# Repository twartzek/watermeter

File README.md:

# WatermeterAI NextGen 💧

Turns a photo of an ordinary analog water meter into a continuous digital reading — no smart meter, no retrofit, just a Raspberry Pi, a camera, and a YOLO model reading the dials like a person would.

Every 15 minutes, a camera photographs the meter's dial face and a pair of YOLO models reads the digit wheels and sweep needles into one cumulative value, which is filtered for outliers, stored, and pushed to a dashboard and MQTT. A nightly job watches the trend for the signature of a leak and emails a warning before it becomes a water bill.

## Contents

- [WatermeterAI NextGen 💧](#watermeterai-nextgen-)
  - [Contents](#contents)
  - [Installation](#installation)
  - [Local development](#local-development)
    - [Verifying a deploy](#verifying-a-deploy)
  - [Configuration reference](#configuration-reference)
  - [How it works](#how-it-works)
  - [Model training](#model-training)
  - [Hardware](#hardware)
    - [What it costs](#what-it-costs)
  - [Leak detection](#leak-detection)
  - [Repository layout](#repository-layout)
  - [Known limitations](#known-limitations)
  - [Credits](#credits)
  - [License](#license)

## Installation

The intended target is a fresh Raspberry Pi OS install (Bullseye or newer, 64-bit recommended for `torch`/`ultralytics`).

```bash
git clone https://github.com/twartzek/watermeter
cd watermeter
sudo bash setupscript.sh
```

`setupscript.sh` is idempotent-ish but not fully — read it before running it twice. It will:

1. Increase swap to 2 GB (YOLO inference is memory-hungry on a Pi Zero 2)
2. Install system packages (`python3-picamera2`, `zbar-tools`, `npm`, `watchdog`)
3. Create a Python venv and install the pinned backend dependencies
4. Write `/home/admin/watermeter/.env` with the paths the backend expects
5. Register two `systemd` services and three cron jobs (measurement every 15 min, leak check nightly, photo cleanup nightly)
   - Readings are kept at full 15-minute resolution forever. At ~100 bytes per row that is only ~4 MB per year, and the leak detector's baseline window (`BASELINE_LOOKBACK_DAYS`, currently 30 days) can be extended if needed.
   - The photos are what fills the SD card, so the nightly cleanup keeps every photo for the last 30 days only. On older days it keeps just the photos of the first and last reading, and it also removes older orphaned photos from failed recognitions.
6. Configure a hardware watchdog that reboots the Pi if the reading log goes stale

Build the frontend once, so the systemd service has something to serve:

```bash
cd frontend
npm install
npm run build   # outputs to frontend/dist, served by `serve` on :80
```

On first boot with no WiFi configured, `backend/wifi.py` waits for a WiFi-credentials QR code (printed on a router, or from any "share WiFi" phone feature) to be shown to the camera — no keyboard or monitor needed.

## Local development

No Pi or camera needed to work on the dashboard/API — `requirements.txt` covers everything else:

```bash
cd backend
python3 -m venv .venv && source .venv/bin/activate
pip install -r requirements.txt

cp .env.example watermeter/.env   # see Configuration reference below
python seed_dev_data.py           # optional: populate SQLite with sample readings
python restapi.py                 # → http://localhost:8000/api/v1
```

```bash
cd frontend
npm install
npm run dev                       # → http://localhost:5173
```

Run the test suite with:

```bash
cd backend
pytest
```

`requirements-pi.txt` (`ultralytics`, `torch`, `opencv-python`, `pyzbar`, `Pillow`) is only needed for the actual image-reading pipeline, on hardware that can run YOLO inference.

### Verifying a deploy

Every frontend build stamps itself with its short git commit hash (`git rev-parse --short HEAD` in [`frontend/vite.config.js`](frontend/vite.config.js), plus `-dirty` for uncommitted changes), shown at the bottom of the dashboard sidebar — compare it against your local `git rev-parse --short HEAD` after `deploy.sh` to confirm the Pi picked up the latest build.

## Configuration reference

Install-specific config lives in two places, both deliberately excluded from version control:

| File | Holds | Set by |
|---|---|---|
| `watermeter/.env` | Filesystem paths — DB file, image folder, log folder, model weight paths | `setupscript.sh` on install |
| `data/settings.json` | MQTT broker credentials, SMTP credentials | Dashboard's Settings page, or manually on first run |

> **Network exposure:** The REST API has permissive CORS and no authentication — built for a trusted home LAN. Don't port-forward `:8000`/`:80` without a reverse proxy and auth in front.

## How it works

```mermaid
flowchart TB
    cam["📷 Pi Camera<br/><small>every 15 min</small>"]
    read["readTotalConsumption.py<br/><small>2× YOLO11<br/>digits + needles</small>"]
    presence["missing-box check<br/><small>discard incomplete reads</small>"]
    filt["outlierDetection.py<br/><small>digit · flow · delta<br/>filters</small>"]
    db[("SQLite<br/><small>readings + images</small>")]
    mqtt["MQTT broker"]
    api["restapi.py<br/><small>FastAPI :8000</small>"]
    dash["React dashboard<br/><small>:80</small>"]
    leak["leakageDetector.py<br/><small>Z-score + Isolation<br/>Forest · daily</small>"]
    warn["✉️ Email + MQTT<br/><small>notifications</small>"]
    wdog["watchdog<br/><small>reboots on hang</small>"]

    cam -->|photo| read
    read -->|raw m³| presence
    presence -->|passed| filt
    filt -->|store| db
    db -->|publish| mqtt
    db -->|read| api
    api -->|JSON| dash
    db -.->|30-day history| leak
    leak -.->|3× flagged| warn
    read -.->|watches for a hang| wdog

    style read fill:#b5672f,color:#fff,stroke:#8a4d22
    style db fill:#b5672f,color:#fff,stroke:#8a4d22
    style api fill:#b5672f,color:#fff,stroke:#8a4d22
    style leak fill:#b5672f,color:#fff,stroke:#8a4d22
```

*Solid arrows run every 15 minutes; dashed arrows (leak detector) run nightly and only speak up after three consecutive flagged days. A watchdog reboots the Pi if a run ever hangs.*

**Reading pipeline.** Two YOLO11 models read the digit wheels and sweep needles into a cumulative m³ value; a red-pixel check locates the decimal point, since the fractional wheels are printed red.

*A real frame from the housing camera: the digit model finds each wheel (`0 0 0 9 3`), the needle model reads the four red dials — together 93.4855 m³.*

**Outlier filtering.** A missing-box check discards incomplete frames outright. Accepted values then pass missing-digit, max-flow (rate + absolute cap), and negative-delta filters — a single bad reading falls back to the local median, but a sustained run of consistent higher readings is accepted as real (e.g. a pipe burst) and triggers a notification instead of being clamped forever.

**Storage and delivery.** Readings, images, and every intermediate pipeline value land in SQLite, publish to MQTT, and are served by FastAPI to the React dashboard. Developer mode exposes each pipeline stage as its own chart line.

## Model training

The two YOLO11 models in `backend/models/` were trained on **3,516 images** from several sources — web photos, synthetically generated dials, and composited images — to cover a wide range of meter appearances, lighting, and angles, so the model doesn't overfit to one setup.

| Model | Task | Precision | Recall | mAP50 | mAP50-95 | Epochs |
|---|---|---|---|---|---|---|
| `totalandneedles/best.pt` | Needle position + counter-area detection | 0.894 | 0.882 | 0.906 | 0.852 | 100 |
| `digits/best.pt` | Digit-wheel detection (0–9 + red/transition class) | 0.964 | 0.908 | 0.948 | 0.826 | 100 |

The higher digit-detection precision (0.96 vs. 0.89) reflects that digit wheels are a more visually consistent target than needle position, which varies more geometrically across meter models. The two models' errors are largely independent, which is part of why the outlier filters downstream catch what either model gets wrong on its own.

If retraining for a different meter design, keep the same split (needles/counter-area vs. digit wheels). Training scripts and the raw dataset aren't included here, but the label format follows standard Ultralytics YOLO conventions — any compatible pipeline (e.g. [Roboflow](https://roboflow.com) or local [Ultralytics](https://docs.ultralytics.com/)) will work.

## Hardware

`Raspberry Pi Zero 2 W (or better)` · `Pi Camera Module` · `Custom LED light (KiCad)` · `3D-printed mount (FreeCAD)`

<p align="center">
  
  &nbsp;&nbsp;
  
</p>
<p align="center"><sub>Left: FreeCAD model · Right: installed on the meter</sub></p>

The camera and a custom LED light source (schematic/PCB in [`hardware/led/`](hardware/led/)) sit inside a 3D-printed bracket ([`mechanics/`](mechanics/)) that clips over the meter's glass face — no plumbing work, no meter replacement. Camera and LED are offset from each other at an angle chosen so the glass's specular reflection is thrown away from the camera instead of back into it, which is the single biggest source of misreads.

### What it costs

The compute and imaging side is deliberately cheap — accuracy comes from the YOLO models and lighting, not the hardware:

| Part | Price |
| --- | --- |
| Raspberry Pi Zero 2 W | ~€20 / $15 |
| Camera module (e.g. RPIZ-CAM-GS) | ~€15 |
| **Total (board + camera)** | **~€35 / ~$40** |

Add a power supply, SD card, the LED board, and a printed bracket (see [`hardware/`](hardware/) and [`mechanics/`](mechanics/)) and you're realistically still under €50 all in. Prices fluctuate by retailer; check current listings.

> **Reproducing the hardware:** PCB and enclosure files are provided as-is. You'll need KiCad for `hardware/led/led.kicad_pcb` and FreeCAD for the `mechanics/*.FCStd` models — expect to adapt the bracket geometry, since glass diameter/depth vary by meter manufacturer.

## Leak detection

`leakageDetector.py` runs nightly and combines three independent signals, since a slow leak, a stuck-open valve, and a burst pipe each look different in the reading history:

| Check | Catches | How |
|---|---|---|
| Rest-period check | Flow that never fully stops in 24h | Looks for any window where consecutive readings stay within an adaptive noise threshold |
| Z-score model | A quiet-hour slot (e.g. 3am) running unusually high | Compares each time-of-day slot's rolling 30-min sum against its own 30-day distribution |
| Isolation Forest | Unusual combinations — steady flow at an odd hour, an odd-sized single spike | Unsupervised model trained on flow, streak length, and time-of-day features |

A single flagged night doesn't trigger a warning — three consecutive nights do, trading a day or two of latency for not emailing you every time the dishwasher runs at an odd hour.

## Repository layout

| Path | What lives there |
|---|---|
| `backend/` | FastAPI server, YOLO reading pipeline, leak detector, SQLite models |
| `backend/models/` | Trained YOLO11 weights (digits, needles+counter-area) |
| `backend/tests/` | Pytest suite — pure-function tests + a DB-backed integration test |
| `frontend/` | React + Vite dashboard (readings, charts, settings, notifications) |
| `hardware/led/` | KiCad schematic + PCB for the LED illumination board |
| `mechanics/` | FreeCAD models for the camera/light 3D-printed mounting bracket |
| `setupscript.sh` | Provisions a fresh Pi: swap, services, cron, watchdog, `.env` |

## Known limitations

- Reading accuracy depends on consistent lighting and a clean meter face — condensation, dirt, or an off-angle mount degrades YOLO's confidence.
- The bundled models were trained on one meter's dial design; a differently styled meter will likely need retraining.
- No authentication on the API or dashboard — see the CORS callout above.
- The Pi Zero 2 W is workable but slow for inference; a Pi 4/5 gives noticeably faster latency.

## Credits

Inspired by [jomjol/AI-on-the-edge-device](https://github.com/jomjol/AI-on-the-edge-device), which pioneered reading analog utility meters with on-device ML on an ESP32. WatermeterAI NextGen takes a different path: a Raspberry Pi's extra headroom, YOLO object detection instead of digit-segment classification, and a camera/LED geometry that avoids glare — aiming for accurate readings straight out of the box, with no per-install calibration.

## License

Backend and hardware design files: MIT — see [`LICENSE`](LICENSE).

The frontend is built on [Reactwind](https://github.com/imarpanpatra/Reactwind) by Arpan Patra, also MIT-licensed — see [`frontend/LICENSE.md`](frontend/LICENSE.md) for its original attribution.

---

Built around one household's water meter. Pull requests that make it work with more meter styles, or that harden the network story, are welcome.

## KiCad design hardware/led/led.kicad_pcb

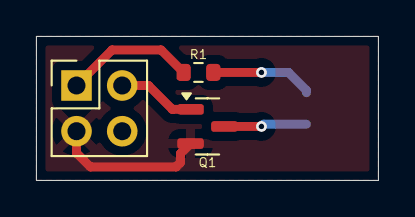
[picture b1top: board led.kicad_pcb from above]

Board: 2 copper layers, 19.0 x 8.0 mm, 4 parts (1 on the bottom side), 5 nets.

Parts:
D1: LED; LED_0603_1608Metric_Pad1.05x0.95mm_HandSolder
J1: Conn_02x02_Odd_Even; PinHeader_2x02_P2.54mm_Vertical
Q1: PDTC123JT; SOT-23
R1: 100; R_0603_1608Metric

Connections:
+5V: J1.1, R1.1
GND: J1.3, Q1.2 (E)
unnamed: D1.2 (A), R1.2
unnamed: D1.1 (K), Q1.3 (C)
unnamed: J1.2, Q1.1 (B)

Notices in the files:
README.md:
License: MIT
